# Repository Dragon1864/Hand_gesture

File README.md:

# Hand_gesture
detecting static hand gesture without using camera module
This a device which predicts static hand gestures using four IR sesnors whcih are placed like a square. 
Top Left              Top Right
Bottom Left           Bottom Right

and using if-esle if  conditions in embedded C we can identify the gestures. 
also added few lines to store the sequence in which the sensor is activated to predict the clockwise and anticlockwise motion.

It uses ESP-32 as the microcontroller here.

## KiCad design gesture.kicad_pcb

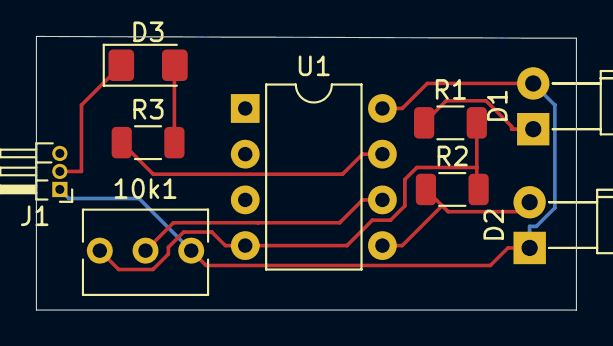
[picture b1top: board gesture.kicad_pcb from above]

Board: 2 copper layers, 30.0 x 15.2 mm, 9 parts (0 on the bottom side), 7 nets.

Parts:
10k1: R_Potentiometer; Potentiometer_Bourns_3266Y_Vertical
D1, D2: LED; LED_D3.0mm_Horizontal_O3.81mm_Z10.0mm
D3: LED; LED_1206_3216Metric_Pad1.42x1.75mm_HandSolder
J1: Conn_01x03_Pin; PinHeader_1x03_P1.00mm_Horizontal
R1: 100; R_1206_3216Metric
R2: 10k; R_1206_3216Metric
R3: 330; R_1206_3216Metric
U1: LM358; DIP-8_W7.62mm

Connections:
+5V: 10k1.1, D1.2 (A), D2.1 (K), J1.1, U1.8 (V+)
GND: 10k1.3, D3.1 (K), J1.2, R1.2, R2.2, U1.4 (V-)
unnamed: D1.1 (K), R1.1
unnamed: D2.2 (A), R2.1, U1.5 (+)
unnamed: R3.1, U1.7
unnamed: 10k1.2, U1.6 (-)
Output: D3.2 (A), R3.2
